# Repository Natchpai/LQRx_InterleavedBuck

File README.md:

# Digitally Controlled Interleaved Buck Converter

Digitally controlled **2-Phase Interleaved Synchronous Buck Converter** utilizing a state-space **Linear Quadratic Regulator** 
Optimized for time-critical embedded deployment at a switching frequency of **200 kHz** using the STM32G474 microcontroller.

---

## 🚀 Key Features

*   **2-Phase Interleaved Topology:** Reduce input and output current ripples, yields a **400 kHz** equivalent ripple, allowing for smaller filter components.
*   **Augmented LQR Control:** Discrete-time State-space control , Integral Action and Delay Compensation.
*   **Hard Execution:** Optimized algorithms execute within **1.8 µs**, inside the 5 µs timing window of the switching cycle.

---

## 📊 Key Specifications

| Parameter | Nominal Value | Note |
| :--- | :--- | :--- |
| **Input Voltage ($V_{in}$)** | 24 VDC | 28V MAX  |
| **Output Voltage ($V_{out}$)** | 12 VDC | Regulated target reference ($V_{ref}$) can changed. |
| **Maximum Load Current** | 20 A (10A per phase) | Rated for **200W+** continuous output capability  |
| **Switching Frequency ($f_{sw}$)** | 200 kHz | **400 kHz** equivalent input/output ripple frequency due to 180° interleaving |
| **Controller Strategy** | State Feedback | Mathematical compensation for discrete execution delay  |
| **Firmware Execution Time** | $\approx 2.2\ \mu s$ | Executed completely within a $5\ \mu s$ timing window |

---

## Hardware

### Power Stage Components
* **High-Side MOSFET**: OptiMOS-6 BSZ018N04LS6
* **Low-Side MOSFET**: OptiMOS-6 IQE013N04LM6
* **Power Inductors**: $10\ \mu\text{H}$
* **Capacitors**: $140\ \mu\text{F}$
  
---

## Control Implementation
1.  **Digital Delay Augmentation:** Mathematically models and compensates for the computation and ADC sampling delays within the state vector to prevent phase-margin degradation.
2.  **Integral Action Augmentation:** Includes an augmented error-integral state to eliminate steady-state tracking error, forcing $V_{out} = V_{ref}$ under varying load conditions.

## License
Copyright (c) 2026 Natchpai.

The hardware design files are licensed under CERN-OHL-W-2.0.

The complete licence text is available in: </br>
[CERN Open Hardware Licence Version 2 - Weakly Reciprocal](LICENSE)  </br>

* **Project Developer** - *Core Hardware, Embedded Firmware & Control Design* - [@Natchpai](https://github.com/Natchpai)

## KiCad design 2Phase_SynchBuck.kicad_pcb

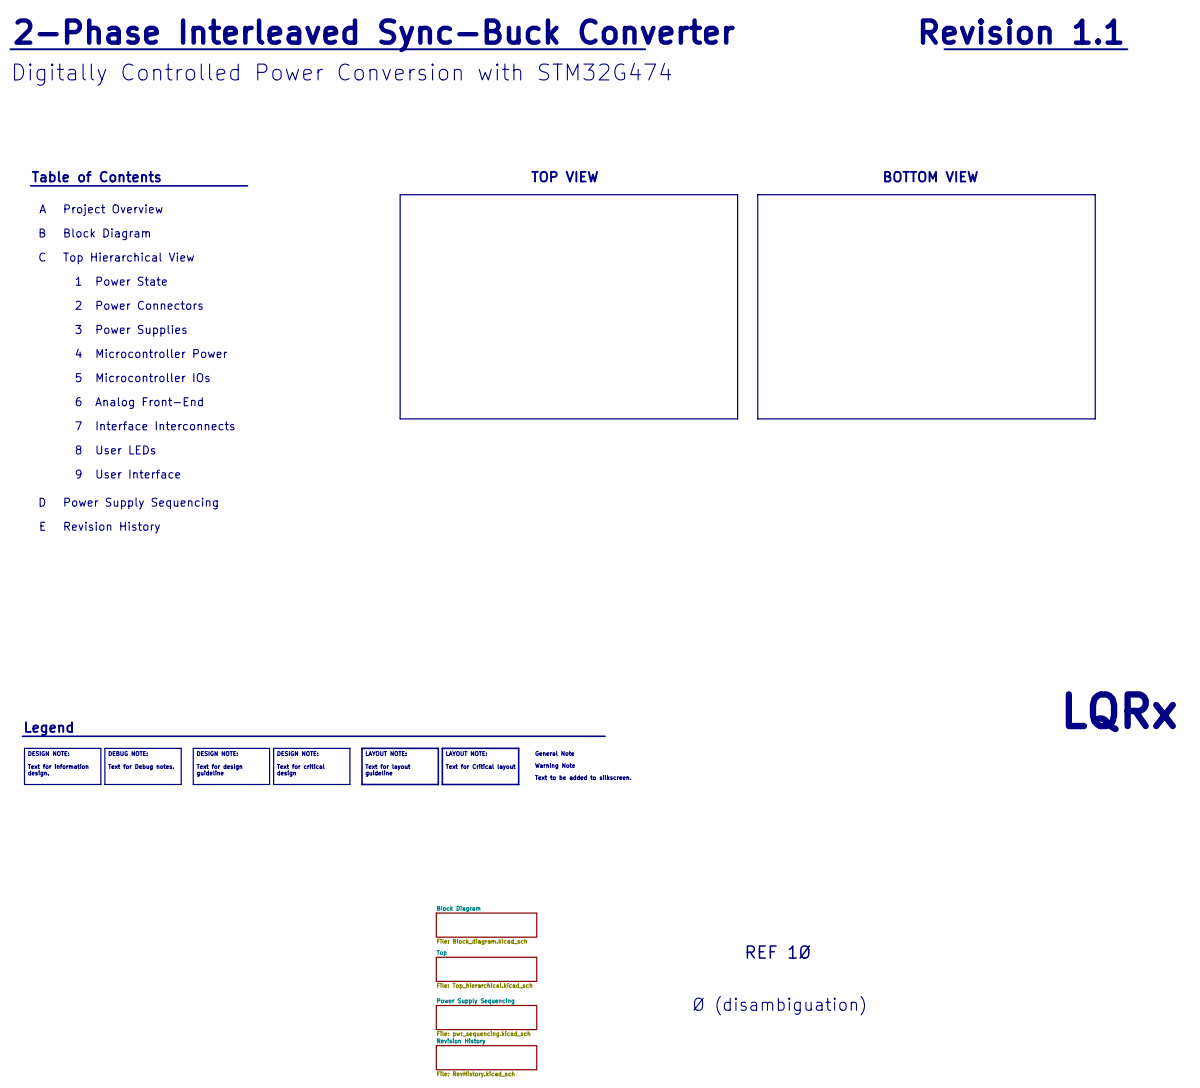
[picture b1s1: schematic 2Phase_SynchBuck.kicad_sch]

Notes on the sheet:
Top Hierarchical View
LQRx
General Note
Warning Note
Power Supplies
Analog Front-End
Microcontroller IOs
User LEDs
Project Overview
Ø (disambiguation)
Legend
Microcontroller Power
Table of Contents
2-Phase Interleaved Sync-Buck Converter
Interface Interconnects
REF 1Ø
TOP VIEW
Revision ${REVISION}
Revision History
BOTTOM VIEW
User Interface
Digitally Controlled Power Conversion with STM32G474
Power Supply Sequencing
Power State
Text to be added to silkscreen.
Block Diagram
Power Connectors
DESIGN NOTE: Text for critical design
LAYOUT NOTE: Text for layout guideline
DESIGN NOTE: Text for information design.
DEBUG NOTE: Text for Debug notes.
LAYOUT NOTE: Text for Critical layout
DESIGN NOTE: Text for design guideline

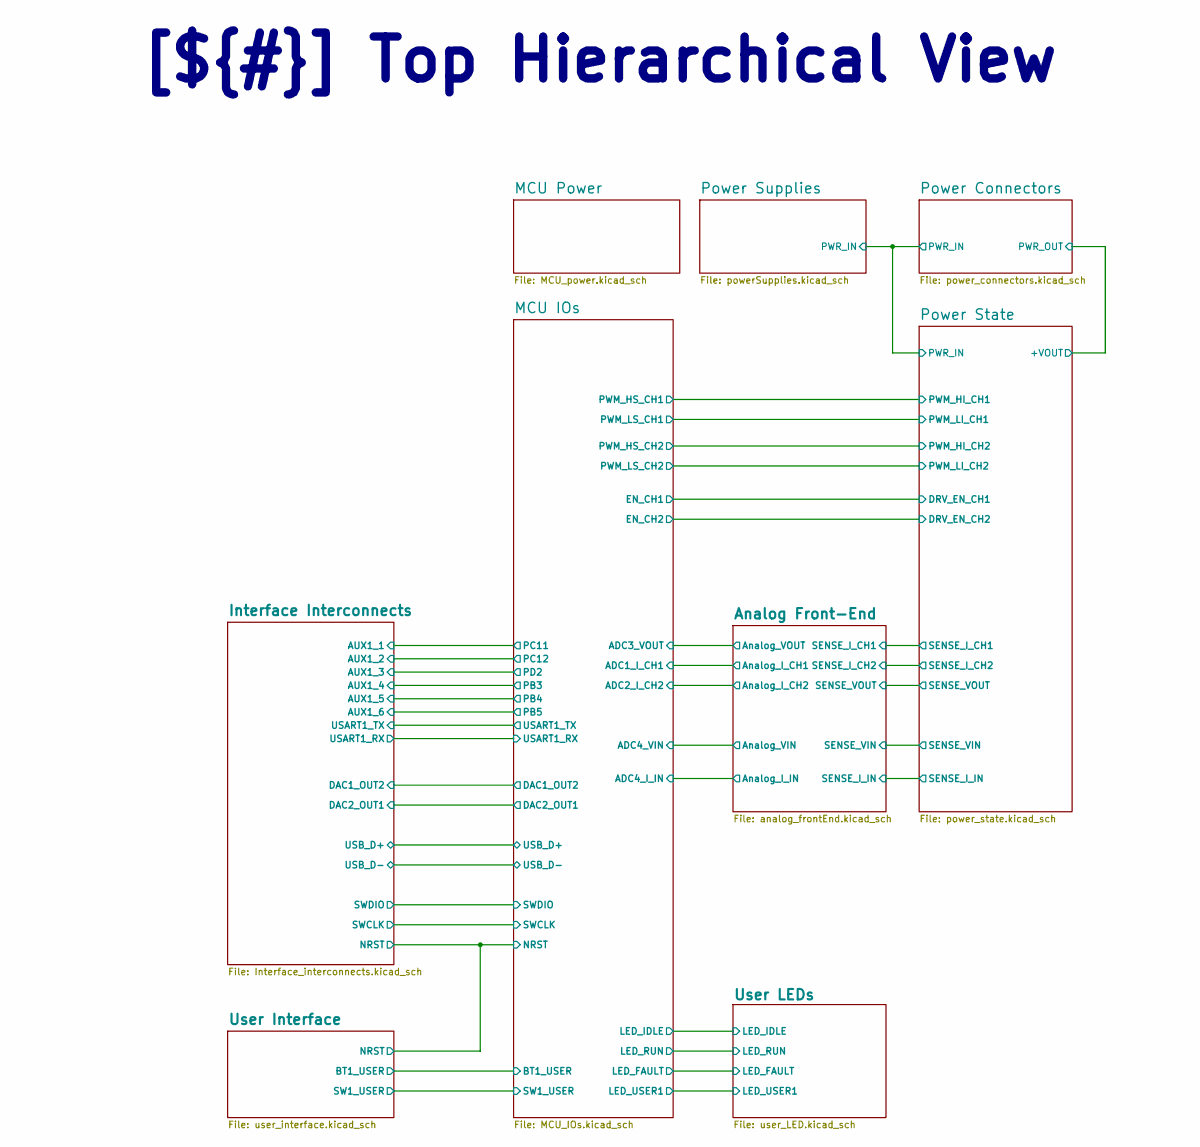
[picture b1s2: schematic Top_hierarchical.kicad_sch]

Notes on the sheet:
[${#}] ${COMMENT1}

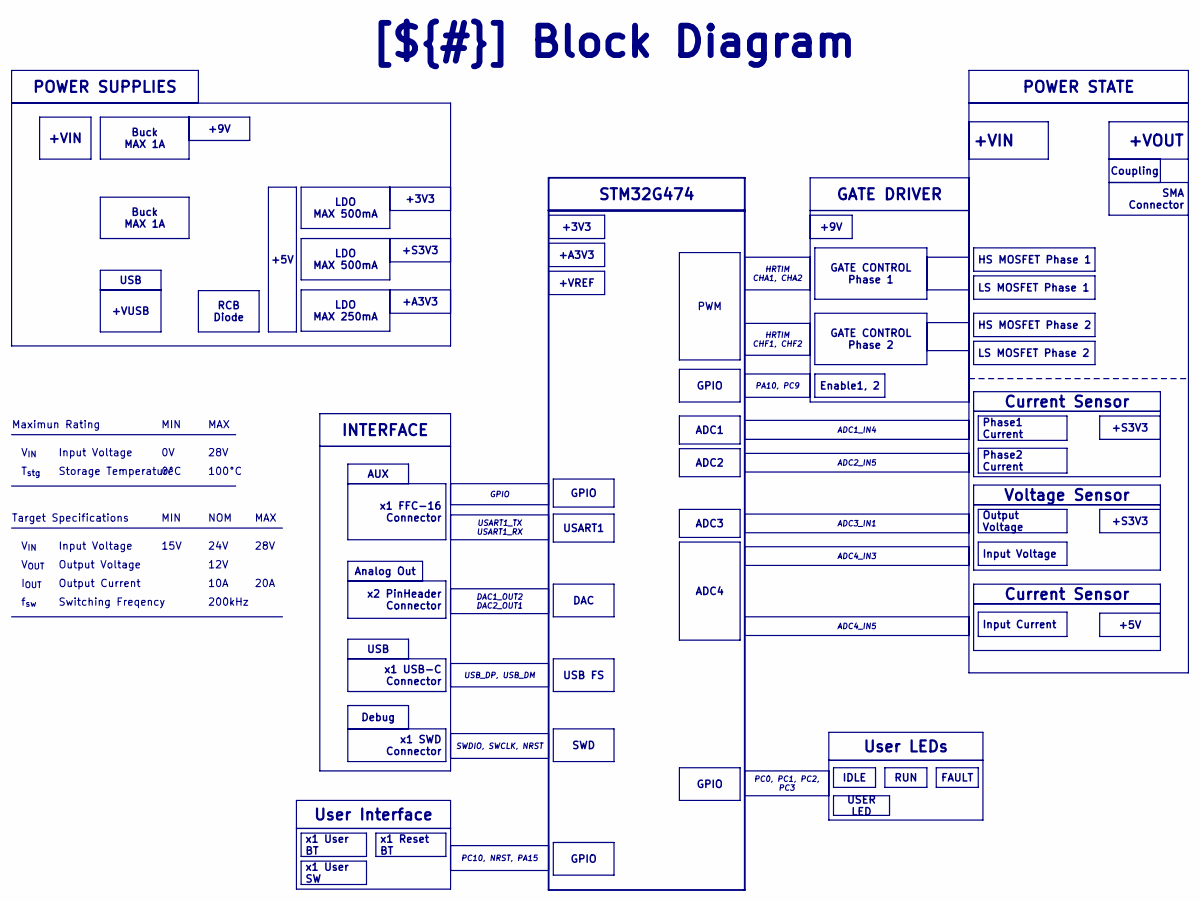
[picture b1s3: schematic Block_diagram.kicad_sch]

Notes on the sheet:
MAX
Output Current
12V
[${#}] ${COMMENT1}
MIN
V_{IN}
Output Voltage
T_{stg}
Target Specifications
100°C
f_{sw}
Storage Temperature
10A
28V
Maximun Rating
24V
0°C
Input Voltage
15V
NOM
200kHz
I_{OUT}
20A
Switching Freqency
V_{OUT}
Analog Out
x2 PinHeader Connector
LDO MAX 250mA
USB_DP, USB_DM
INTERFACE
+A3V3
DAC
+S3V3
USB
USART1
GATE CONTROL Phase 1
LS MOSFET Phase 1
FAULT
Current Sensor
PC0, PC1, PC2, PC3

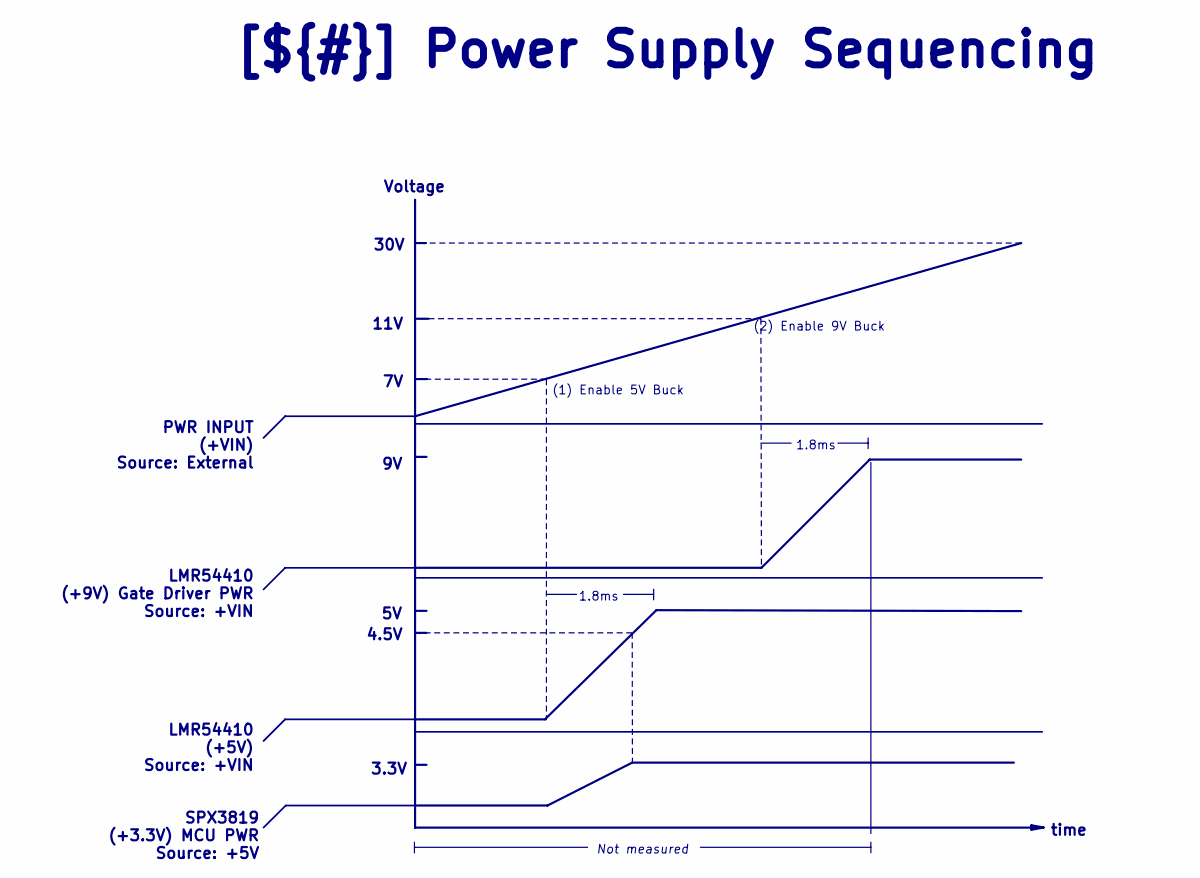
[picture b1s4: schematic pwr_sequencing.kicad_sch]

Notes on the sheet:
4.5V
SPX3819 (+3.3V) MCU PWR Source: +5V
[${#}] ${COMMENT1}
(1) Enable 5V Buck
Voltage
30V
1.8ms
PWR INPUT (+VIN) Source: External
11V
3.3V
time
Not measured
LMR54410 (+9V) Gate Driver PWR Source: +VIN
LMR54410 (+5V) Source: +VIN
(2) Enable 9V Buck

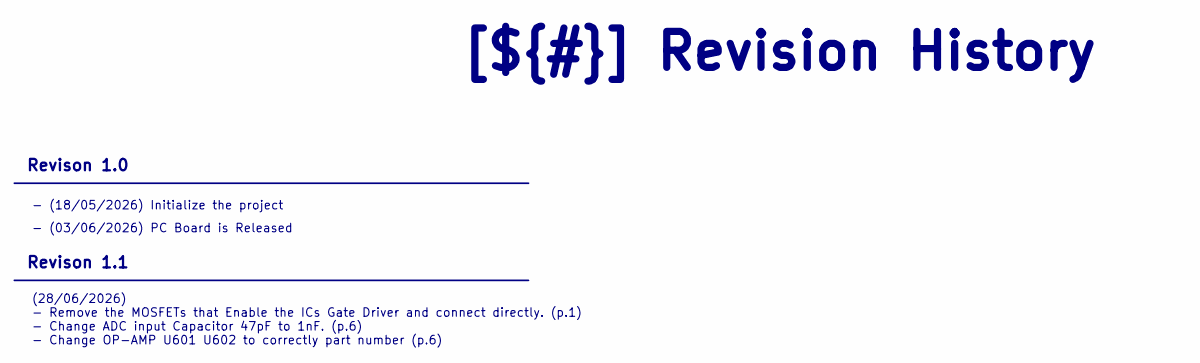
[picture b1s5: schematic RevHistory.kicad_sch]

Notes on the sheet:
(28/06/2026) - Remove the MOSFETs that Enable the ICs Gate Driver and connect directly. (p.1) - Change ADC input Capacitor 47pF to 1nF. (p.6) - Change OP-AMP U601 U602 to correctly part number (p.6)
- (18/05/2026) Initialize the project
[${#}] ${COMMENT1}
Revison 1.1
Revison 1.0
- (03/06/2026) PC Board is Released

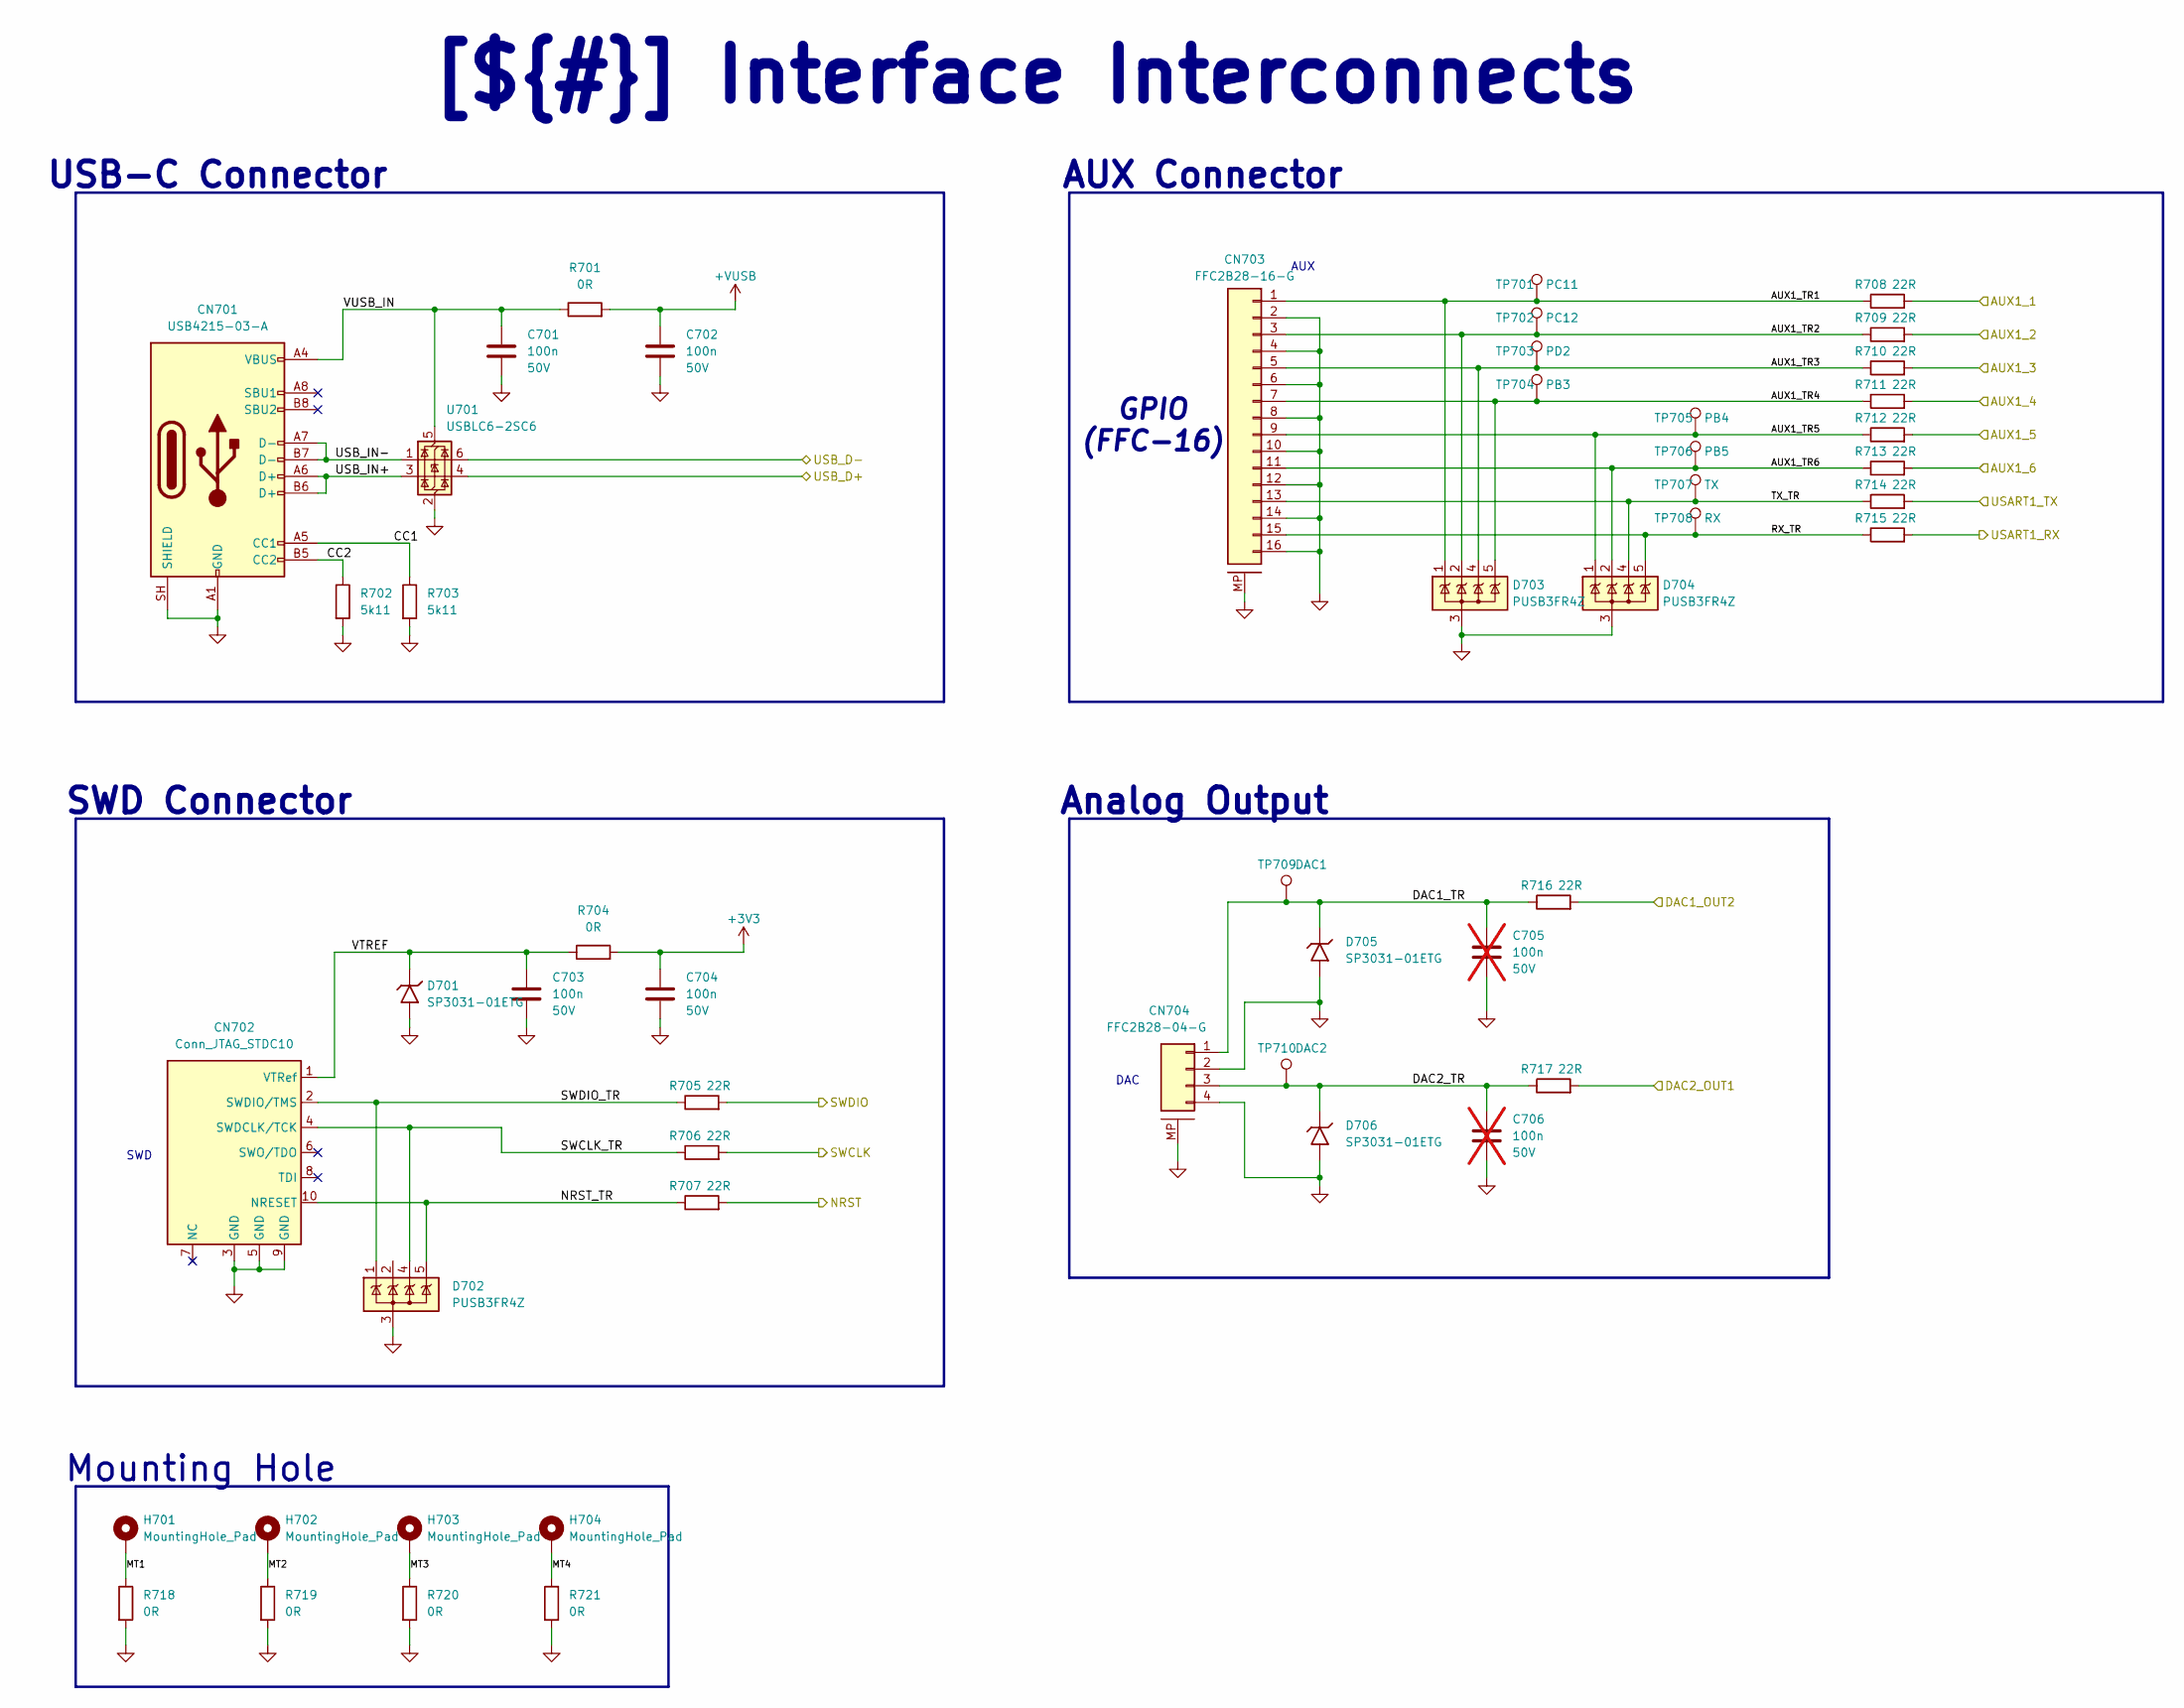
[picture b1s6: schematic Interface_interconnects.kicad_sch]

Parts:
C701, C702, C703, C704: 100n; C_0402_nomDensity; Manufacturer Part Number GRM155R71H104KE14D
C705, C706: 100n; C_0402_nomDensity; Manufacturer Part Number GRM155R71H104KE14D; not fitted
CN701: USB4215-03-A; USB_C_Receptacle_GCT_USB4215-03-A_16P_TopMnt_Horizontal; Manufacturer Part Number USB4215-03-A
CN702: Conn_JTAG_STDC10; BD_2x05_P1.27mm_Vertical_SMD; Manufacturer Part Number BD125-10-A-0305-0580-L-B
CN703: FFC2B28-16-G; GCT_FFC2B28-16_P0.5_FFC-16; Manufacturer Part Number FFC2B28-16-G
CN704: FFC2B28-04-G; GCT_FFC2B28-04_P0.5_FFC-4; Manufacturer Part Number FFC2B28-04-G
D701, D705, D706: SP3031-01ETG; D_SOD-882; Manufacturer Part Number SP3031-01ETG
D702, D703, D704: PUSB3FR4Z; SOT1176-2-_1x2.5mm_P0.5mm; Manufacturer Part Number PUSB3FR4Z
H701, H702, H703, H704: MountingHole_Pad; MountingHole_3.2mm_M3_Pad_Via
R701, R704, R718, R719, R720, R721: 0R; R_0603_nomDensity; Manufacturer Part Number RC0603JR-070RL
R702, R703: 5k11; R_0402_nomDensity; Manufacturer Part Number RC0402FR-135K11L
R705, R706, R707, R708, R709, R710, R711, R712, R713, R714, R715, R716, R717: 22R; R_0402_nomDensity; Manufacturer Part Number RC0402FR-1322RL
TP701: PC11; TestPoint_NoSlik_D0.5mm_Top
TP702: PC12; TestPoint_NoSlik_D0.5mm_Top
TP703: PD2; TestPoint_NoSlik_D0.5mm_Top
TP704: PB3; TestPoint_NoSlik_D0.5mm_Top
TP705: PB4; TestPoint_NoSlik_D0.5mm_Top
TP706: PB5; TestPoint_NoSlik_D0.5mm_Top
TP707: TX; TestPoint_NoSlik_D0.5mm_Top
TP708: RX; TestPoint_NoSlik_D0.5mm_Top
TP709: DAC1; TestPoint_NoSlik_D0.5mm_Top
TP710: DAC2; TestPoint_NoSlik_D0.5mm_Top
U701: USBLC6-2SC6; SOT-23-6; Manufacturer Part Number USBLC6-2SC6

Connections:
+3V3: C704.1, R704.2; also elsewhere on the board
+VUSB: C702.1, R701.2; also elsewhere on the board
/Top/Interface Interconnects/AUX1_TR1: CN703.1, D703.1 (K), D703.10, R708.1, TP701.1 (1_1)
/Top/Interface Interconnects/AUX1_TR2: CN703.3, D703.2 (K), D703.9, R709.1, TP702.1 (1_1)
/Top/Interface Interconnects/AUX1_TR3: CN703.5, D703.4 (K), D703.7, R710.1, TP703.1 (1_1)
/Top/Interface Interconnects/AUX1_TR4: CN703.7, D703.5 (K), D703.6, R711.1, TP704.1 (1_1)
/Top/Interface Interconnects/AUX1_TR5: CN703.9, D704.1 (K), D704.10, R712.1, TP705.1 (1_1)
/Top/Interface Interconnects/AUX1_TR6: CN703.11, D704.2 (K), D704.9, R713.1, TP706.1 (1_1)
/Top/Interface Interconnects/CC1: CN701.A5 (CC1), R703.1
/Top/Interface Interconnects/CC2: CN701.B5 (CC2), R702.1
/Top/Interface Interconnects/DAC1_TR: C705.1, CN704.1, D705.1, R716.1, TP709.1 (1_1)
/Top/Interface Interconnects/DAC2_TR: C706.1, CN704.3, D706.1, R717.1, TP710.1 (1_1)
/Top/Interface Interconnects/MT1: H701.1 (1_1), R718.1
/Top/Interface Interconnects/MT2: H702.1 (1_1), R719.1
/Top/Interface Interconnects/MT3: H703.1 (1_1), R720.1
/Top/Interface Interconnects/MT4: H704.1 (1_1), R721.1
/Top/Interface Interconnects/NRST_TR: CN702.10 (NRESET), D702.5 (K), D702.6, R707.1
/Top/Interface Interconnects/RX_TR: CN703.15, D704.5 (K), D704.6, R715.1, TP708.1 (1_1)
/Top/Interface Interconnects/SWCLK_TR: CN702.4 (SWDCLK/TCK), D702.4 (K), D702.7, R706.1
/Top/Interface Interconnects/SWDIO_TR: CN702.2 (SWDIO/TMS), D702.1 (K), D702.10, R705.1
/Top/Interface Interconnects/TX_TR: CN703.13, D704.4 (K), D704.7, R714.1, TP707.1 (1_1)
/Top/Interface Interconnects/USB_IN+: CN701.A6 (D+), CN701.B6 (D+), U701.3 (I/O2)
/Top/Interface Interconnects/USB_IN-: CN701.A7 (D-), CN701.B7 (D-), U701.1 (I/O1)
/Top/Interface Interconnects/VTREF: C703.1, CN702.1 (VTRef), D701.1, R704.1
/Top/Interface Interconnects/VUSB_IN: C701.1, CN701.A4 (VBUS), CN701.A9 (VBUS), CN701.B4 (VBUS), CN701.B9 (VBUS), R701.1, U701.5 (VBUS)
/Top/MCU IOs/DAC1_OUT2: R716.2; also elsewhere on the board
/Top/MCU IOs/DAC2_OUT1: R717.2; also elsewhere on the board
/Top/MCU IOs/NRST: R707.2; also elsewhere on the board
/Top/MCU IOs/PB3: R711.2; also elsewhere on the board
/Top/MCU IOs/PB4: R712.2; also elsewhere on the board
/Top/MCU IOs/PB5: R713.2; also elsewhere on the board
/Top/MCU IOs/PC11: R708.2; also elsewhere on the board
/Top/MCU IOs/PC12: R709.2; also elsewhere on the board
/Top/MCU IOs/PD2: R710.2; also elsewhere on the board
/Top/MCU IOs/SWCLK: R706.2; also elsewhere on the board
/Top/MCU IOs/SWDIO: R705.2; also elsewhere on the board
/Top/MCU IOs/USART1_RX: R715.2; also elsewhere on the board
/Top/MCU IOs/USART1_TX: R714.2; also elsewhere on the board
/Top/MCU IOs/USB_D+: U701.4 (I/O2); also elsewhere on the board
/Top/MCU IOs/USB_D-: U701.6 (I/O1); also elsewhere on the board
GND: C701.2, C702.2, C703.2, C704.2, C705.2, C706.2, CN701.A1 (GND), CN701.A12 (GND), CN701.B1 (GND), CN701.B12 (GND), CN701.SH (SHIELD), CN702.3 (GND), CN702.5 (GND), CN702.9 (GND), CN703.2, CN703.4, CN703.6, CN703.8, CN703.10, CN703.12, CN703.14, CN703.16, CN703.MP (MountPin), CN704.2, CN704.4, CN704.MP (MountPin), D701.2, D702.3 (A), D702.8 (A), D703.3 (A), D703.8 (A), D704.3 (A), D704.8 (A), D705.2, D706.2, R702.2, R703.2, R718.2, R719.2, R720.2, R721.2, U701.2 (GND); also elsewhere on the board
unnamed: D702.2 (K), D702.9

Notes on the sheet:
SWD
SWD Connector
[${#}] ${COMMENT1}
AUX Connector
USB-C Connector
GPIO (FFC-16)
AUX
Mounting Hole
Analog Output
DAC

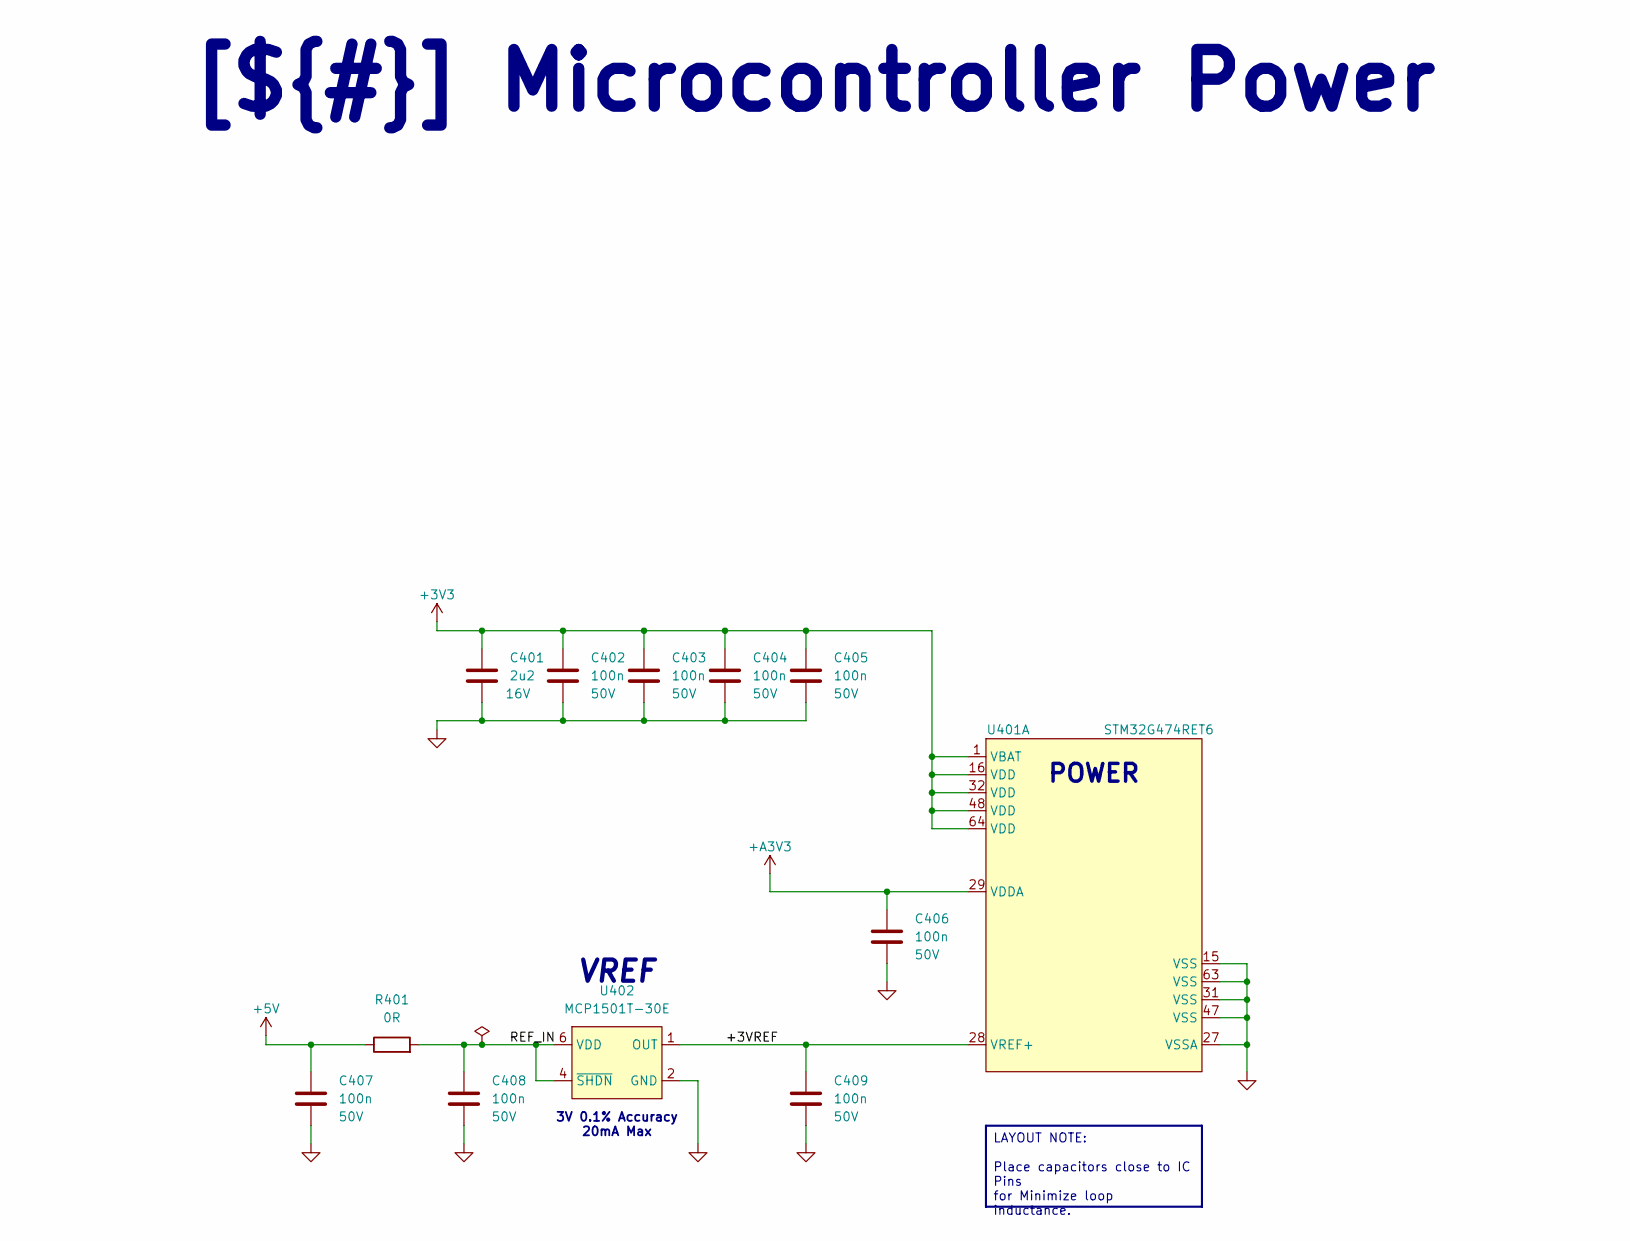
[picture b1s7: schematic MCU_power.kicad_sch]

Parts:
C401: 2u2; C_0603_nomDensity; Manufacturer Part Number GRM188Z71C225KE43
C402, C403, C404, C405, C406, C407, C408, C409: 100n; C_0402_nomDensity; Manufacturer Part Number GRM155R71H104KE14D
R401: 0R; R_0603_nomDensity; Manufacturer Part Number RC0603JR-070RL
U401: STM32G474RET6; LQFP-64_10x10mm_P0.5mm; Manufacturer Part Number STM32G474RET6
U402: MCP1501T-30E; SOT-23-6; Manufacturer Part Number MCP1501T-30E

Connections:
+3V3: C401.1, C402.1, C403.1, C404.1, C405.1, U401.1 (VBAT), U401.16 (VDD), U401.32 (VDD), U401.48 (VDD), U401.64 (VDD); also elsewhere on the board
+5V: C407.1, R401.1; also elsewhere on the board
+A3V3: C406.1, U401.29 (VDDA); also elsewhere on the board
/Top/MCU Power/+3VREF: C409.1, U401.28 (VREF+), U402.1 (OUT)
/Top/MCU Power/REF_IN: C408.1, R401.2, U402.4 (~SHDN), U402.6 (VDD)
GND: C401.2, C402.2, C403.2, C404.2, C405.2, C406.2, C407.2, C408.2, C409.2, U401.15 (VSS), U401.27 (VSSA), U401.31 (VSS), U401.47 (VSS), U401.63 (VSS), U402.2 (GND), U402.3 (GND), U402.5 (GND); also elsewhere on the board

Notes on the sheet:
VREF
3V 0.1% Accuracy 20mA Max
POWER
[${#}] ${COMMENT1}
LAYOUT NOTE: Place capacitors close to IC Pins for Minimize loop inductance.

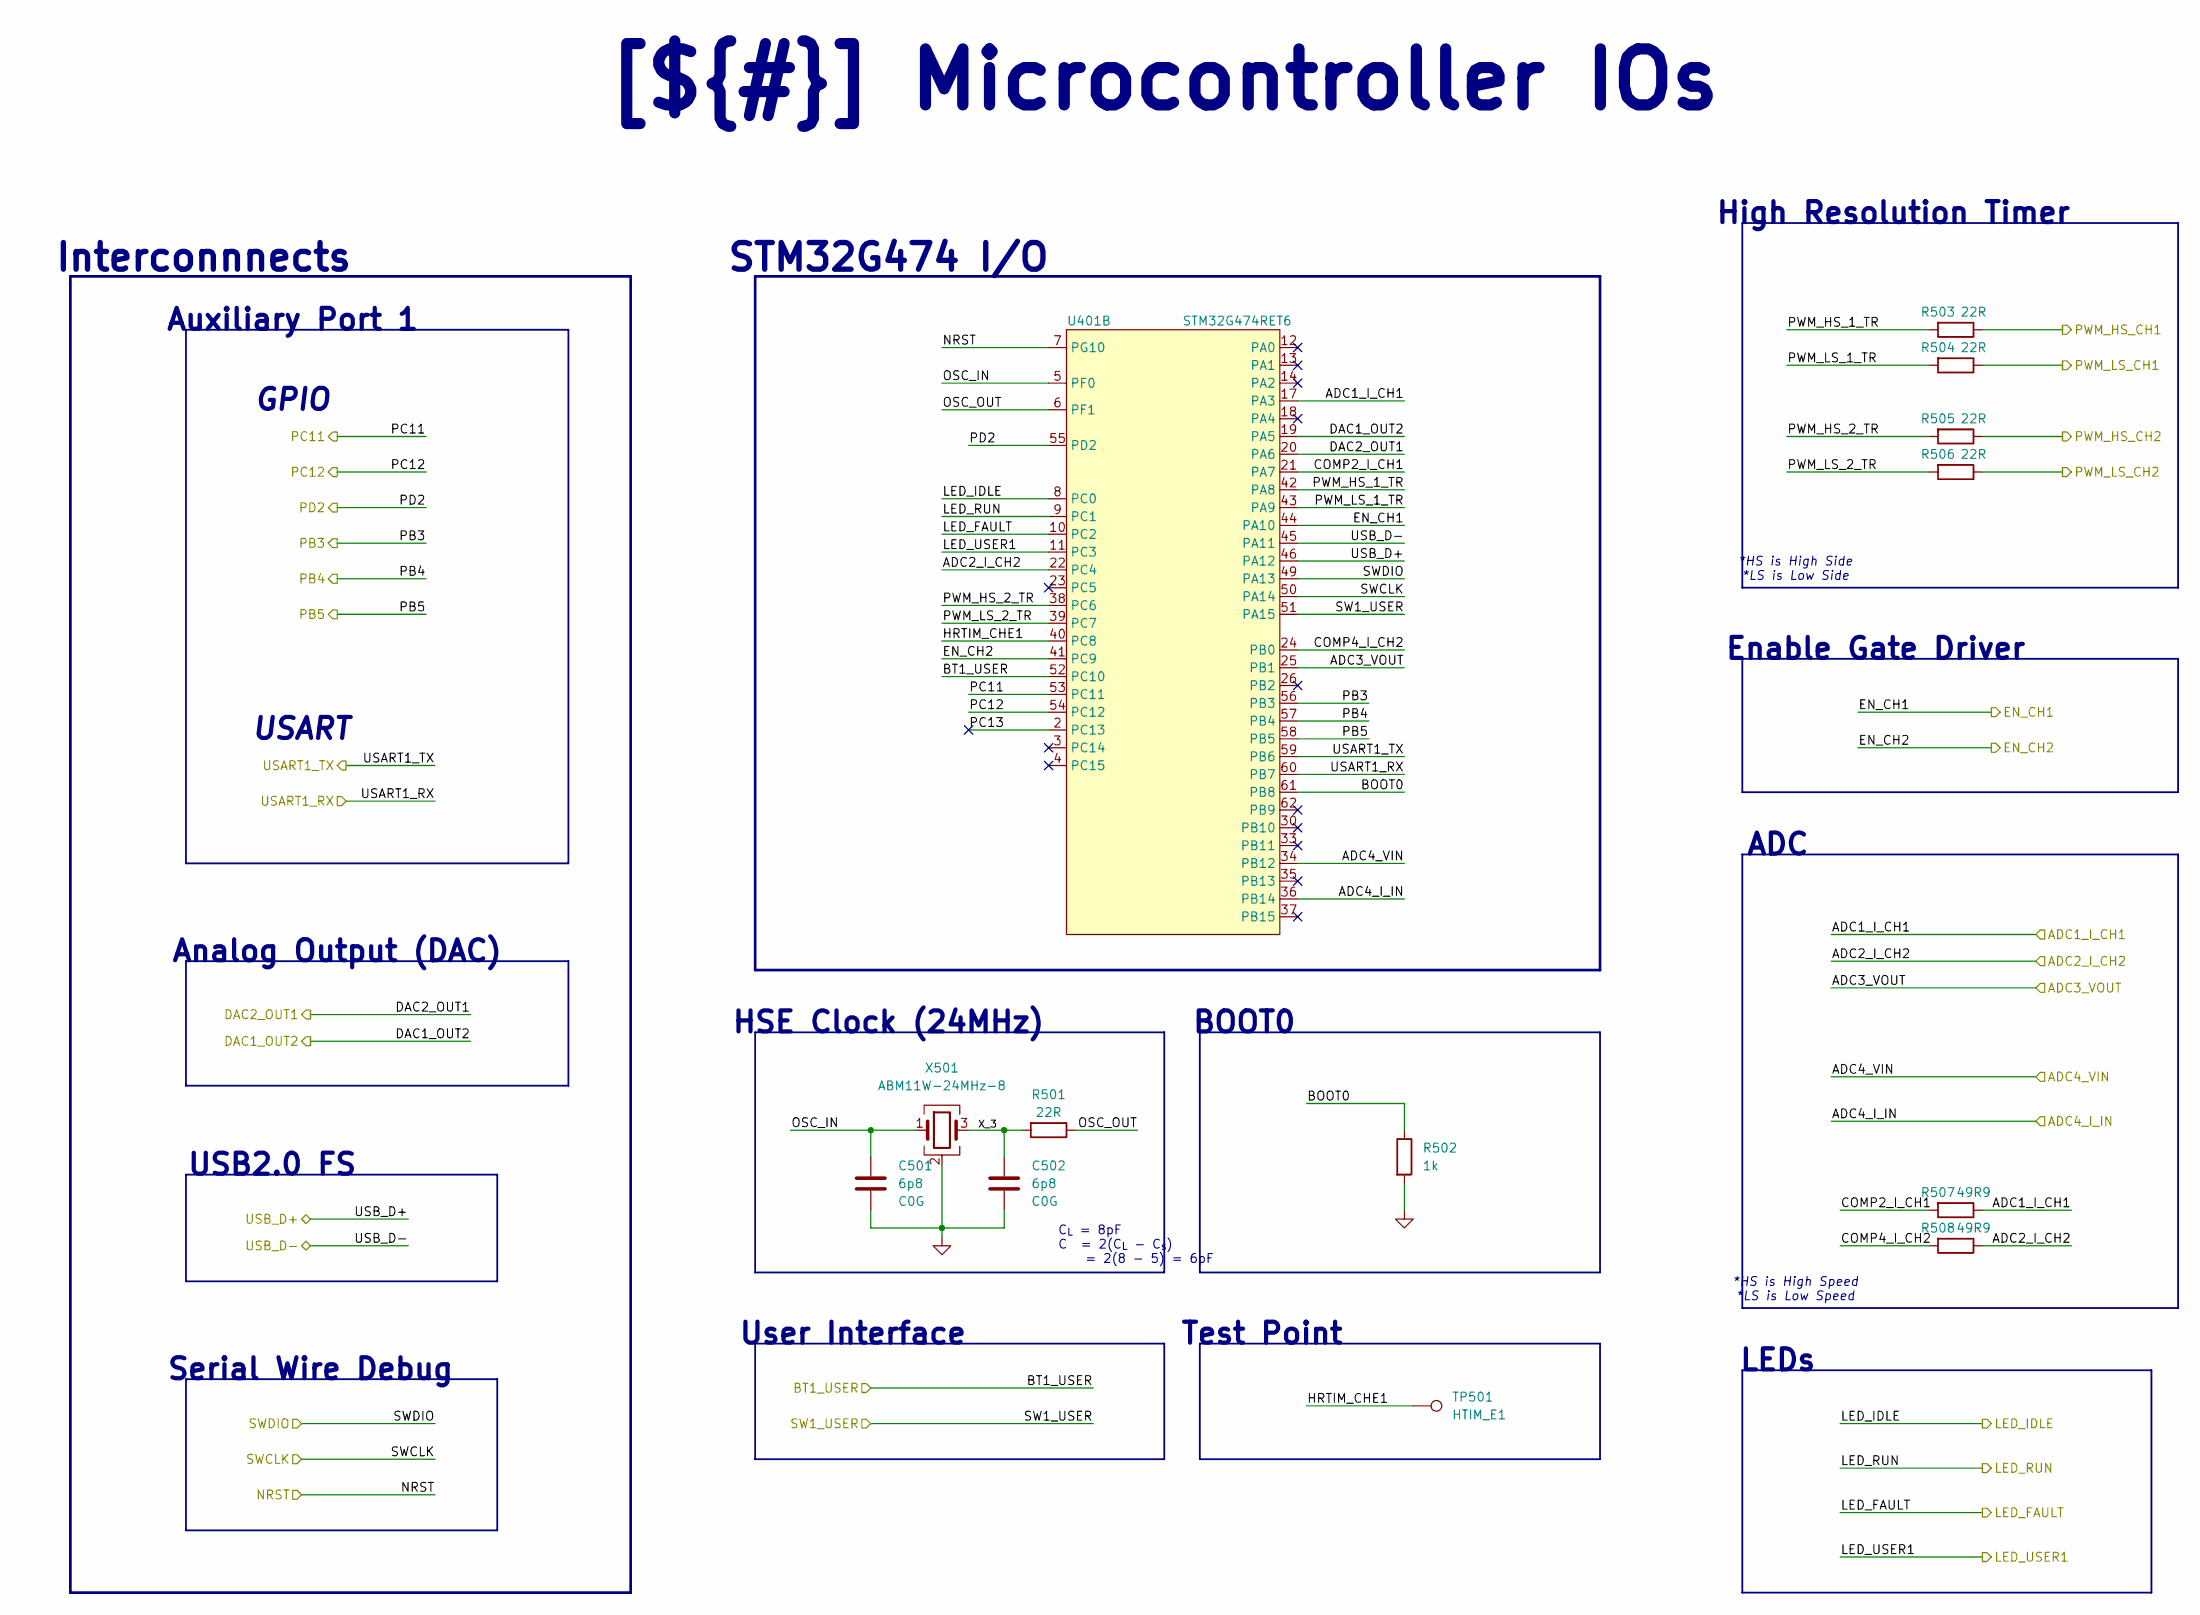
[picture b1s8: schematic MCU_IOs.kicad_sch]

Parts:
C501, C502: 6p8; C_0402_nomDensity; Manufacturer Part Number GCM1555C1H6R8FA16D
R501, R503, R504, R505, R506: 22R; R_0402_nomDensity; Manufacturer Part Number RC0402FR-1322RL
R502: 1k; R_0402_nomDensity; Manufacturer Part Number RC0402FR-071KL
R507, R508: 49R9; R_0402_nomDensity; Manufacturer Part Number RC0402FR-1349R9L
TP501: HTIM_E1; TestPoint_NoSlik_D1.0mm_Bottom
U401: STM32G474RET6; LQFP-64_10x10mm_P0.5mm; Manufacturer Part Number STM32G474RET6
X501: ABM11W-24MHz-8; ABM11W_2.0x1.6mm; Manufacturer Part Number ABM11W-24.0000MHZ-8-B1U-T3

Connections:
/Top/MCU IOs/ADC1_I_CH1: R507.1, U401.17 (PA3); also elsewhere on the board
/Top/MCU IOs/ADC2_I_CH2: R508.1, U401.22 (PC4); also elsewhere on the board
/Top/MCU IOs/ADC3_VOUT: U401.25 (PB1); also elsewhere on the board
/Top/MCU IOs/ADC4_I_IN: U401.36 (PB14); also elsewhere on the board
/Top/MCU IOs/ADC4_VIN: U401.34 (PB12); also elsewhere on the board
/Top/MCU IOs/BOOT0: R502.1, U401.61 (PB8)
/Top/MCU IOs/BT1_USER: U401.52 (PC10); also elsewhere on the board
/Top/MCU IOs/COMP2_I_CH1: R507.2, U401.21 (PA7)
/Top/MCU IOs/COMP4_I_CH2: R508.2, U401.24 (PB0)
/Top/MCU IOs/DAC1_OUT2: U401.19 (PA5); also elsewhere on the board
/Top/MCU IOs/DAC2_OUT1: U401.20 (PA6); also elsewhere on the board
/Top/MCU IOs/EN_CH1: U401.44 (PA10); also elsewhere on the board
/Top/MCU IOs/EN_CH2: U401.41 (PC9); also elsewhere on the board
/Top/MCU IOs/HRTIM_CHE1: TP501.1 (1_1), U401.40 (PC8)
/Top/MCU IOs/LED_FAULT: U401.10 (PC2); also elsewhere on the board
/Top/MCU IOs/LED_IDLE: U401.8 (PC0); also elsewhere on the board
/Top/MCU IOs/LED_RUN: U401.9 (PC1); also elsewhere on the board
/Top/MCU IOs/LED_USER1: U401.11 (PC3); also elsewhere on the board
/Top/MCU IOs/NRST: U401.7 (PG10); also elsewhere on the board
/Top/MCU IOs/OSC_IN: C501.1, U401.5 (PF0), X501.1
/Top/MCU IOs/OSC_OUT: R501.1, U401.6 (PF1)
/Top/MCU IOs/PB3: U401.56 (PB3); also elsewhere on the board
/Top/MCU IOs/PB4: U401.57 (PB4); also elsewhere on the board
/Top/MCU IOs/PB5: U401.58 (PB5); also elsewhere on the board
/Top/MCU IOs/PC11: U401.53 (PC11); also elsewhere on the board
/Top/MCU IOs/PC12: U401.54 (PC12); also elsewhere on the board
/Top/MCU IOs/PC13: U401.2 (PC13)
/Top/MCU IOs/PD2: U401.55 (PD2); also elsewhere on the board
/Top/MCU IOs/PWM_HS_1_TR: R503.2, U401.42 (PA8)
/Top/MCU IOs/PWM_HS_2_TR: R505.2, U401.38 (PC6)
/Top/MCU IOs/PWM_HS_CH1: R503.1; also elsewhere on the board
/Top/MCU IOs/PWM_HS_CH2: R505.1; also elsewhere on the board
/Top/MCU IOs/PWM_LS_1_TR: R504.2, U401.43 (PA9)
/Top/MCU IOs/PWM_LS_2_TR: R506.2, U401.39 (PC7)
/Top/MCU IOs/PWM_LS_CH1: R504.1; also elsewhere on the board
/Top/MCU IOs/PWM_LS_CH2: R506.1; also elsewhere on the board
/Top/MCU IOs/SW1_USER: U401.51 (PA15); also elsewhere on the board
/Top/MCU IOs/SWCLK: U401.50 (PA14); also elsewhere on the board
/Top/MCU IOs/SWDIO: U401.49 (PA13); also elsewhere on the board
/Top/MCU IOs/USART1_RX: U401.60 (PB7); also elsewhere on the board
/Top/MCU IOs/USART1_TX: U401.59 (PB6); also elsewhere on the board
/Top/MCU IOs/USB_D+: U401.46 (PA12); also elsewhere on the board
/Top/MCU IOs/USB_D-: U401.45 (PA11); also elsewhere on the board
/Top/MCU IOs/X_3: C502.1, R501.2, X501.3
GND: C501.2, C502.2, R502.2, X501.2 (G), X501.4 (G); also elsewhere on the board

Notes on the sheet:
Serial Wire Debug
Enable Gate Driver
GPIO
C_{L} = 8pF C = 2(C_{L} - C_{s}) = 2(8 - 5) = 6pF
BOOT0
HSE Clock (24MHz)
[${#}] ${COMMENT1}
ADC
Interconnnects
USART
*HS is High Speed *LS is Low Speed
*HS is High Side *LS is Low Side
STM32G474 I/O
USB2.0 FS
Analog Output (DAC)
Auxiliary Port 1
High Resolution Timer
Test Point
User Interface
LEDs
